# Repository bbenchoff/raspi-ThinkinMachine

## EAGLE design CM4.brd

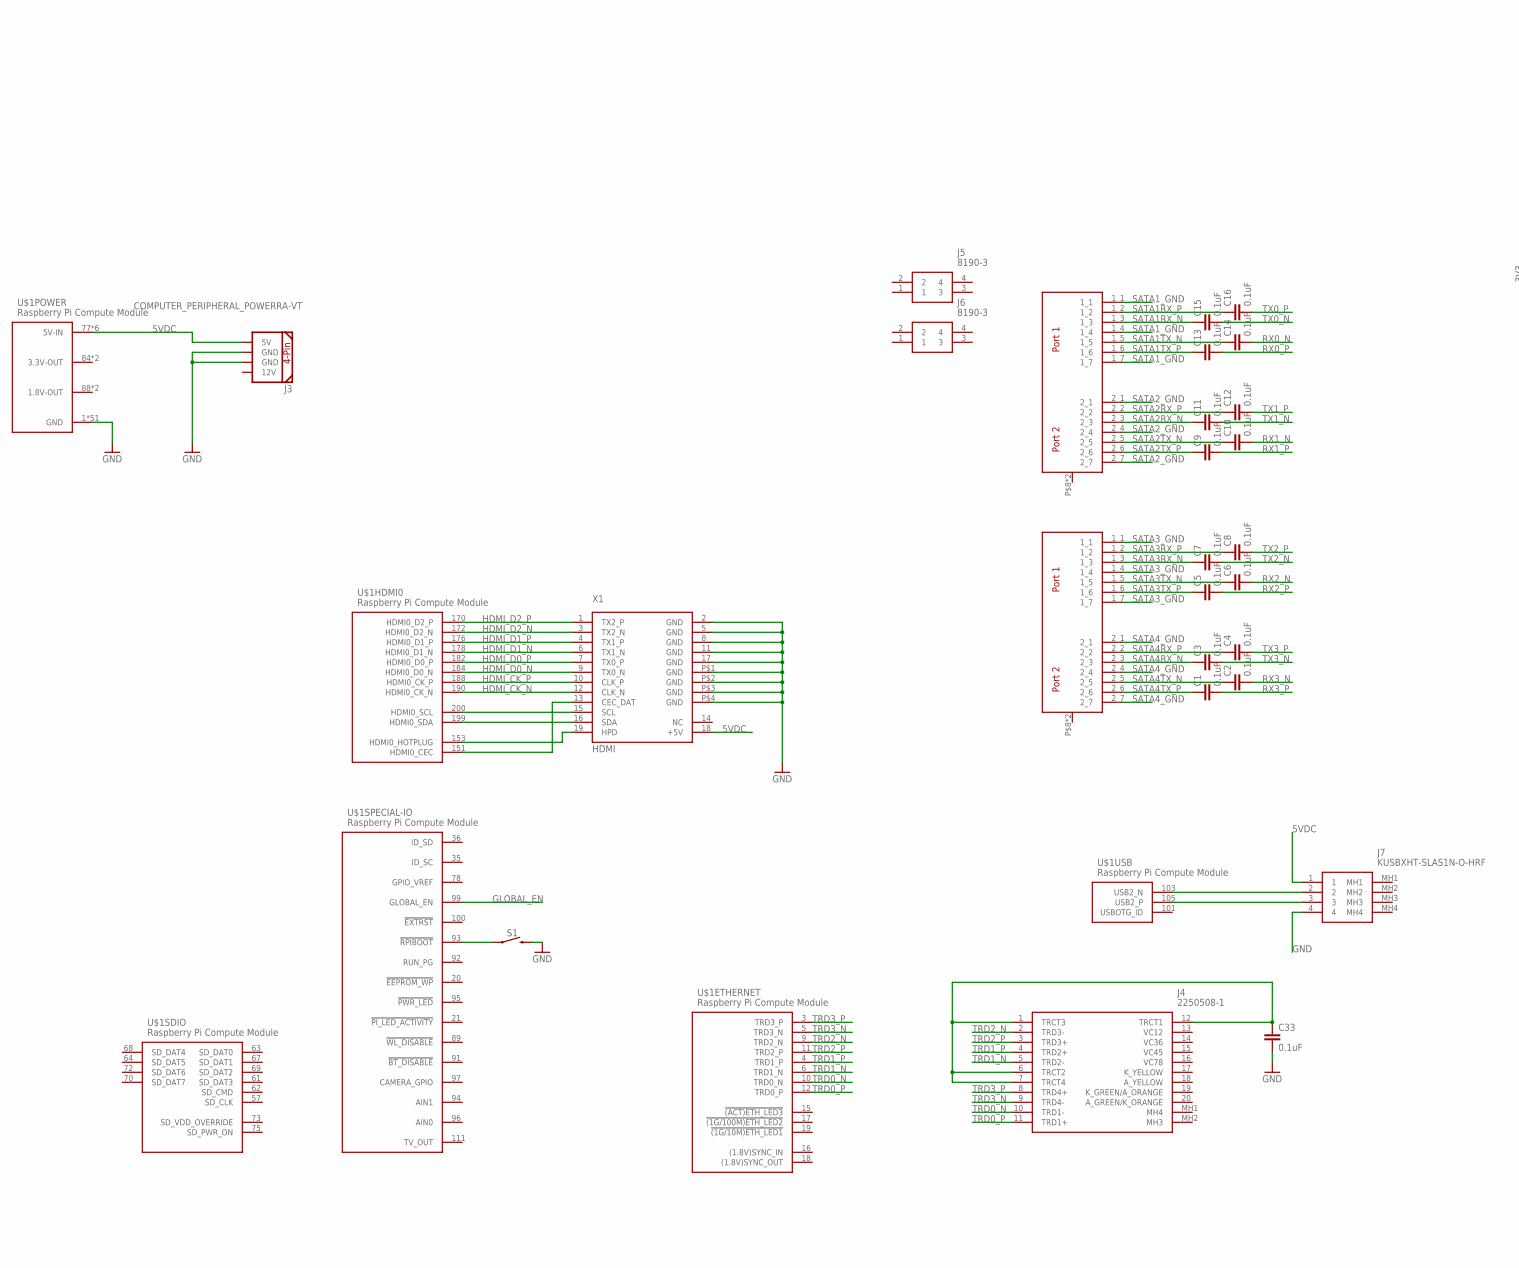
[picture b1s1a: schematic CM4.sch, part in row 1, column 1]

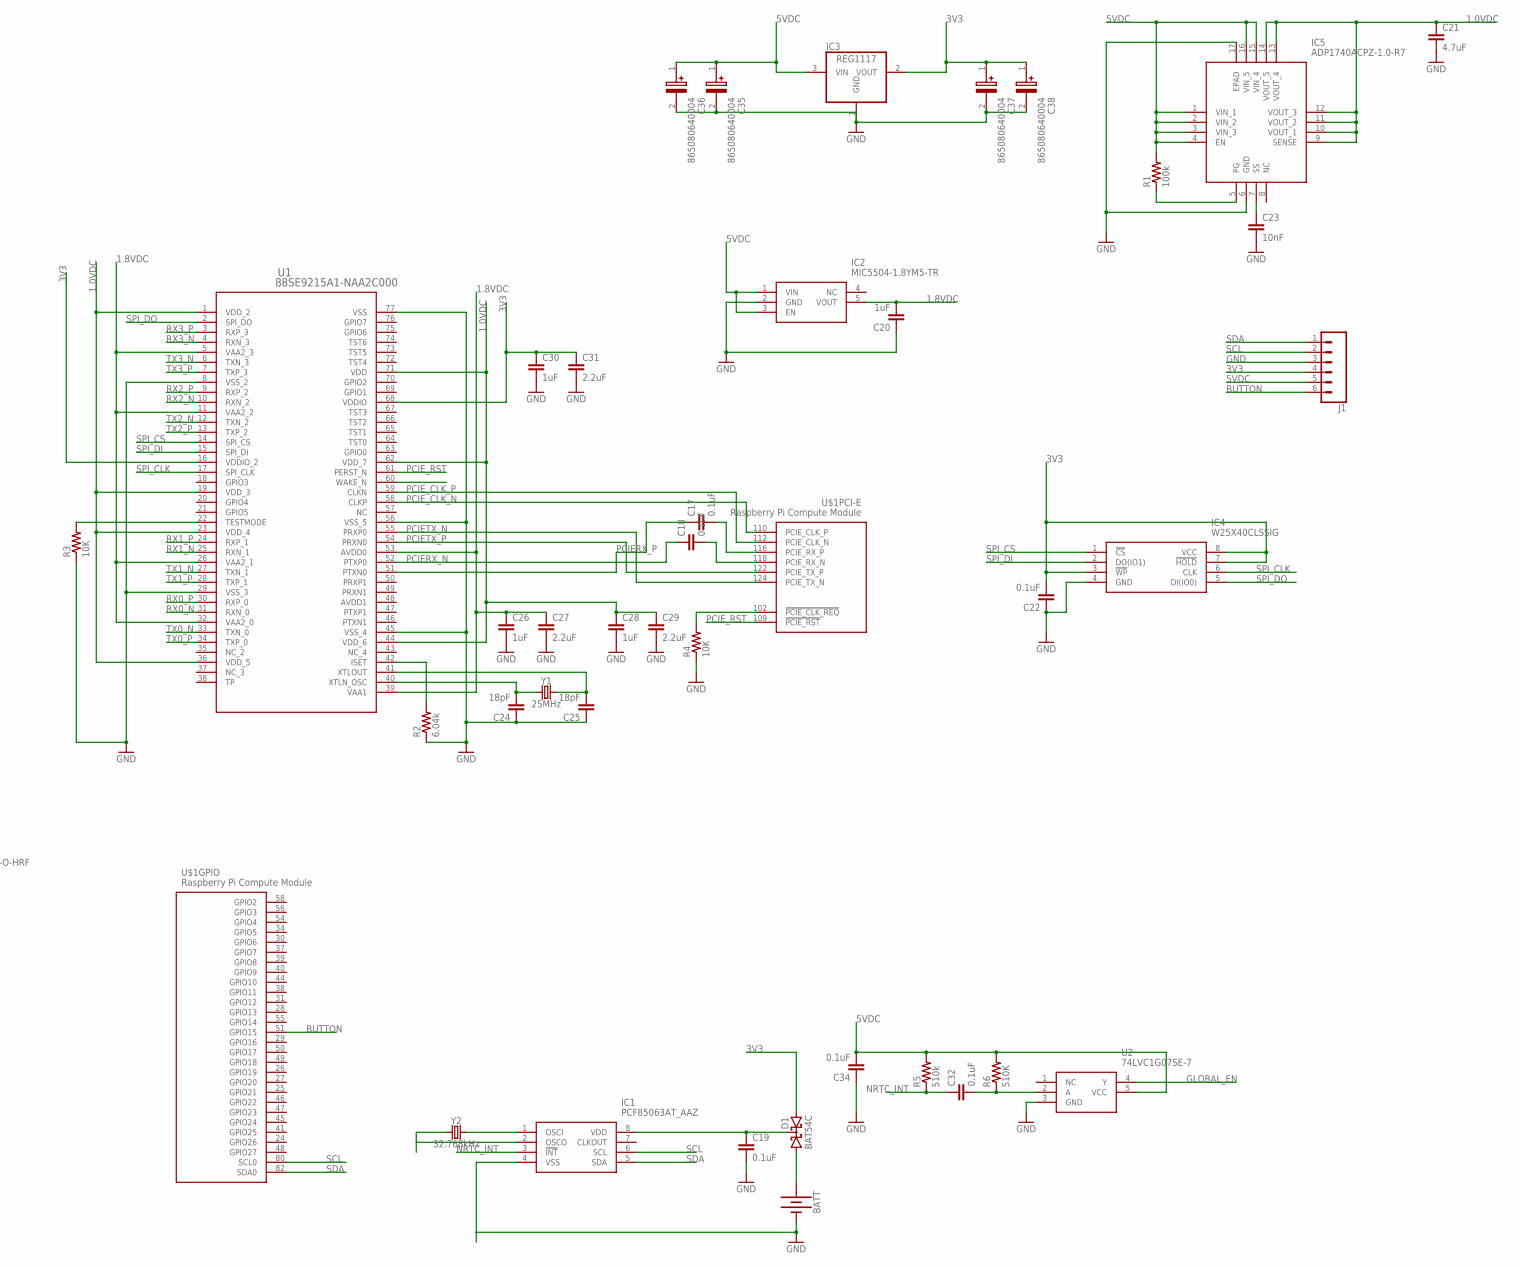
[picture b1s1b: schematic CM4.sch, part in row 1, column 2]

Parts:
BATT: BATTERY-12MM_SMD; BATTCON_12MM
C1, C2, C3, C4, C5, C6, C7, C8, C9, C10, C11, C12, C13, C14, C15, C16, C17, C18, C19, C22, C32, C33, C34: 0.1uF; 0603
C20, C26, C28, C30: 1uF; 0603
C21: 4.7uF; 0603
C23: 10nF; 0603
C24, C25: 18pF; 0603
C27, C29, C31: 2.2uF; 0603
C35, C36, C37, C38: 865080640004
D1: BAT54C; SOT23
IC1: PCF85063AT_AAZ; SOIC127P600X175-8N
IC2: MIC5504-1.8YM5-TR; SOT95P280X145-5N
IC3: REG1117; SOT223
IC4: W25X40CLSSIG; SOIC127P790X216-8N
IC5: ADP1740ACPZ-1.0-R7; QFN65P400X400X80-17N
J1: CONN_06LOCK; 1X06_LOCK
J3: COMPUTER_PERIPHERAL_POWERRA-VT; COMPUTER-PERIPHERAL-POWER-RA-VT
J4: 2250508-1; 22505081
J5, J6: 8190-3; 81903
J7: KUSBXHT-SLAS1N-O-HRF; KUSBXHTSLAS1NOHRF
R1: 100k; R0603
R2: 6.04k; R0603
R3, R4: 10K; R0603
R5: 510k; R0603
R6: 510K; R0603
S1: MOMENTARY-SWITCH-SPST-SMD-5.2-REDUNDANT; TACTILE_SWITCH_SMD_5.2MM
U1: 88SE9215A1-NAA2C000; QFN76_9X9_MTG
U2: 74LVC1G07SE-7; SOT65P210X110-5N
U$1: Raspberry Pi Compute Module; RASPBERRYPI-CM4
U$2, U$3: SATA-D-PL-RT; RIGHTANGLE2PORTSATA
X1: HDMI
Y1: 25MHz; CRYSTAL-SMD-2.0X1.6MM
Y2: 32.768kHz; CRYSTAL-SMD-3.2X1.5MM

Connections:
1.0VDC: C21.1, C28.1, C29.1, IC5.9 (SENSE), IC5.10 (VOUT_1), IC5.11 (VOUT_2), IC5.12 (VOUT_3), IC5.13 (VOUT_4), IC5.14 (VOUT_5), U1.1 (VDD_2), U1.19 (VDD_3), U1.23 (VDD_4), U1.36 (VDD_5), U1.44 (VDD_6), U1.62 (VDD_7), U1.71 (VDD)
1.8V-OUT: U$1.88 (1.8V-OUT), U$1.90 (1.8V-OUT)
1.8VDC: C20.2, C26.1, C27.1, IC2.5 (VOUT), U1.5 (VAA2_3), U1.11 (VAA2_2), U1.26 (VAA2_1), U1.32 (VAA2_0), U1.39 (VAA1), U1.53 (AVDD0)
3.3V-OUT: U$1.84 (3.3V-OUT), U$1.86 (3.3V-OUT)
3V3: C22.2, C30.1, C31.1, C37.1 (+), C38.1 (+), D1.2 (A2), IC3.2 (VOUT), IC4.3 (!WP), IC4.7 (!HOLD), IC4.8 (VCC), J1.4, U1.16 (VDDIO_2), U1.68 (VDDIO)
5VDC: C34.2, C35.1 (+), C36.1 (+), IC2.1 (VIN), IC2.3 (EN), IC3.3 (VIN), IC5.1 (VIN_1), IC5.2 (VIN_2), IC5.3 (VIN_3), IC5.4 (EN), IC5.15 (VIN_4), IC5.16 (VIN_5), J1.5, J3.5V, J7.1, R1.2, R5.2, R6.2, U2.5 (VCC), U$1.77 (5V-IN), U$1.79 (5V-IN), U$1.81 (5V-IN), U$1.83 (5V-IN), U$1.85 (5V-IN), U$1.87 (5V-IN), X1.18 (+5V)
AVDD1: U1.48 (AVDD1)
BUTTON: J1.6, U$1.51 (GPIO15)
GLOBAL_EN: U2.4 (Y), U$1.99 (GLOBAL_EN)
GND: BATT.GND (-), C19.2, C20.1, C21.2, C22.1, C23.2, C24.1, C25.1, C26.2, C27.2, C28.2, C29.2, C30.2, C31.2, C33.2, C34.1, C35.2 (-), C36.2 (-), C37.2 (-), C38.2 (-), IC1.4 (VSS), IC2.2 (GND), IC3.1 (GND), IC4.4 (GND), IC5.6 (GND), IC5.17 (EPAD), J1.3, J3.GND@1 (GND), J3.GND@2 (GND), J7.4, R2.1, R3.1, R4.1, S1.3 (2), S1.4 (2), U1.8 (VSS_2), U1.29 (VSS_3), U1.45 (VSS_4), U1.56 (VSS_5), U1.77 (VSS), U2.3 (GND), U$1.1 (GND), U$1.2 (GND), U$1.7 (GND), U$1.8 (GND), U$1.13 (GND), U$1.14 (GND), U$1.22 (GND), U$1.23 (GND), U$1.32 (GND), U$1.33 (GND), U$1.42 (GND), U$1.43 (GND), U$1.52 (GND), U$1.53 (GND), U$1.59 (GND), U$1.60 (GND), U$1.65 (GND), U$1.66 (GND), U$1.71 (GND), U$1.74 (GND), U$1.98 (GND), U$1.107 (GND), U$1.108 (GND), U$1.113 (GND), U$1.114 (GND), U$1.119 (GND), U$1.120 (GND), U$1.125 (GND), U$1.126 (GND), U$1.131 (GND), U$1.132 (GND), U$1.137 (GND), U$1.138 (GND), U$1.144 (GND), U$1.150 (GND), U$1.155 (GND), U$1.156 (GND), U$1.161 (GND), U$1.162 (GND), U$1.167 (GND), U$1.168 (GND), U$1.173 (GND), U$1.174 (GND), U$1.179 (GND), U$1.180 (GND), U$1.185 (GND), U$1.186 (GND), U$1.191 (GND), U$1.192 (GND), U$1.197 (GND), U$1.198 (GND), X1.2 (GND), X1.5 (GND), X1.8 (GND), X1.11 (GND), X1.17 (GND), X1.P$1 (GND), X1.P$2 (GND), X1.P$3 (GND), X1.P$4 (GND)
HDMI_CK_N: U$1.190 (HDMI0_CK_N), X1.12 (CLK_N)
HDMI_CK_P: U$1.188 (HDMI0_CK_P), X1.10 (CLK_P)
HDMI_D0_N: U$1.184 (HDMI0_D0_N), X1.9 (TX0_N)
HDMI_D0_P: U$1.182 (HDMI0_D0_P), X1.7 (TX0_P)
HDMI_D1_N: U$1.178 (HDMI0_D1_N), X1.6 (TX1_N)
HDMI_D1_P: U$1.176 (HDMI0_D1_P), X1.4 (TX1_P)
HDMI_D2_N: U$1.172 (HDMI0_D2_N), X1.3 (TX2_N)
HDMI_D2_P: U$1.170 (HDMI0_D2_P), X1.1 (TX2_P)
unnamed: C23.1, IC5.7 (SS)
unnamed: IC5.5 (PG), R1.1
unnamed: C24.2, U1.40 (XTLN_OSC), Y1.1
unnamed: C25.2, U1.41 (XTLOUT), Y1.3 (2)
unnamed: C33.1, J4.1 (TRCT3), J4.6 (TRCT2), J4.7 (TRCT4), J4.12 (TRCT1)
unnamed: S1.1, S1.2 (1), U$1.93 (!RPIBOOT)
unnamed: R2.2, U1.42 (ISET)
unnamed: U$1.200 (HDMI0_SCL), X1.15 (SCL)
unnamed: U$1.199 (HDMI0_SDA), X1.16 (SDA)
unnamed: U$1.153 (HDMI0_HOTPLUG), X1.19 (HPD)
unnamed: U$1.151 (HDMI0_CEC), X1.13 (CEC_DAT)
unnamed: IC1.1 (OSCI), Y2.P$2 (2)
unnamed: IC1.2 (OSCO), Y2.P$1 (1)
unnamed: C32.2, R6.1, U2.2 (A)
unnamed: J7.2, U$1.103 (USB2_N)
unnamed: J7.3, U$1.105 (USB2_P)
unnamed: BATT.PWR@1 (+), D1.1 (A1)
unnamed: C19.1, D1.3 (CC), IC1.8 (VDD)
unnamed: R3.2, U1.22 (TESTMODE)
unnamed: R4.2, U$1.102 (!PCIE_CLK_REQ)
NRTC_INT: C32.1, IC1.3 (!INT), R5.1
PCIERXCAP_N: C18.2, U$1.118 (PCIE_RX_N)
PCIERXCAP_P: C17.2, U$1.116 (PCIE_RX_P)
PCIERX_N: C18.1, U1.52 (PTXP0)
PCIERX_P: C17.1, U1.51 (PTXN0)
PCIETX_N: U1.55 (PRXP0), U$1.124 (PCIE_TX_N)
PCIETX_P: U1.54 (PRXN0), U$1.122 (PCIE_TX_P)
PCIE_CLK_N: U1.58 (CLKP), U$1.110 (PCIE_CLK_P)
PCIE_CLK_P: U1.59 (CLKN), U$1.112 (PCIE_CLK_N)
PCIE_RST: U1.61 (PERST_N), U$1.109 (!PCIE_RST)
RX0_N: C14.2, U1.31 (RXN_0)
RX0_P: C13.2, U1.30 (RXP_0)
RX1_N: C10.2, U1.25 (RXN_1)
RX1_P: C9.2, U1.24 (RXP_1)
RX2_N: C6.2, U1.10 (RXN_2)
RX2_P: C5.2, U1.9 (RXP_2)
RX3_N: C2.2, U1.4 (RXN_3)
RX3_P: C1.2, U1.3 (RXP_3)
SATA1RX_N: C15.1, U$2.1_3
SATA1RX_P: C16.1, U$2.1_2
SATA1TX_N: C14.1, U$2.1_5
SATA1TX_P: C13.1, U$2.1_6
SATA1_GND: U$2.1_1, U$2.1_4, U$2.1_7
SATA2RX_N: C11.1, U$2.2_3
SATA2RX_P: C12.1, U$2.2_2
SATA2TX_N: C10.1, U$2.2_5
SATA2TX_P: C9.1, U$2.2_6
SATA2_GND: U$2.2_1, U$2.2_4, U$2.2_7
SATA3RX_N: C7.1, U$3.1_3
SATA3RX_P: C8.1, U$3.1_2
SATA3TX_N: C6.1, U$3.1_5
SATA3TX_P: C5.1, U$3.1_6
SATA3_GND: U$3.1_1, U$3.1_4, U$3.1_7
SATA4RX_N: C3.1, U$3.2_3
SATA4RX_P: C4.1, U$3.2_2
SATA4TX_N: C2.1, U$3.2_5
SATA4TX_P: C1.1, U$3.2_6
SATA4_GND: U$3.2_1, U$3.2_4, U$3.2_7
SCL: IC1.6 (SCL), J1.2, U$1.80 (SCL0)
SDA: IC1.5 (SDA), J1.1, U$1.82 (SDA0)
SPI_CLK: IC4.6 (CLK), U1.17 (SPI_CLK)
SPI_CS: IC4.1 (!CS), U1.14 (SPI_CS)
SPI_DI: IC4.2 (DO(IO1)), U1.15 (SPI_DI)
SPI_DO: IC4.5 (DI(IO0)), U1.2 (SPI_DO)
TRD0_N: J4.10 (TRD1-), U$1.10 (TRD0_N)
TRD0_P: J4.11 (TRD1+), U$1.12 (TRD0_P)
TRD1_N: J4.5 (TRD2-), U$1.6 (TRD1_N)
TRD1_P: J4.4 (TRD2+), U$1.4 (TRD1_P)
TRD2_N: J4.2 (TRD3-), U$1.9 (TRD2_N)
TRD2_P: J4.3 (TRD3+), U$1.11 (TRD2_P)
TRD3_N: J4.9 (TRD4-), U$1.5 (TRD3_N)
TRD3_P: J4.8 (TRD4+), U$1.3 (TRD3_P)
TX0_N: C15.2, U1.33 (TXN_0)
TX0_P: C16.2, U1.34 (TXP_0)
TX1_N: C11.2, U1.27 (TXN_1)
TX1_P: C12.2, U1.28 (TXP_1)
TX2_N: C7.2, U1.12 (TXN_2)
TX2_P: C8.2, U1.13 (TXP_2)
TX3_N: C3.2, U1.6 (TXN_3)
TX3_P: C4.2, U1.7 (TXP_3)

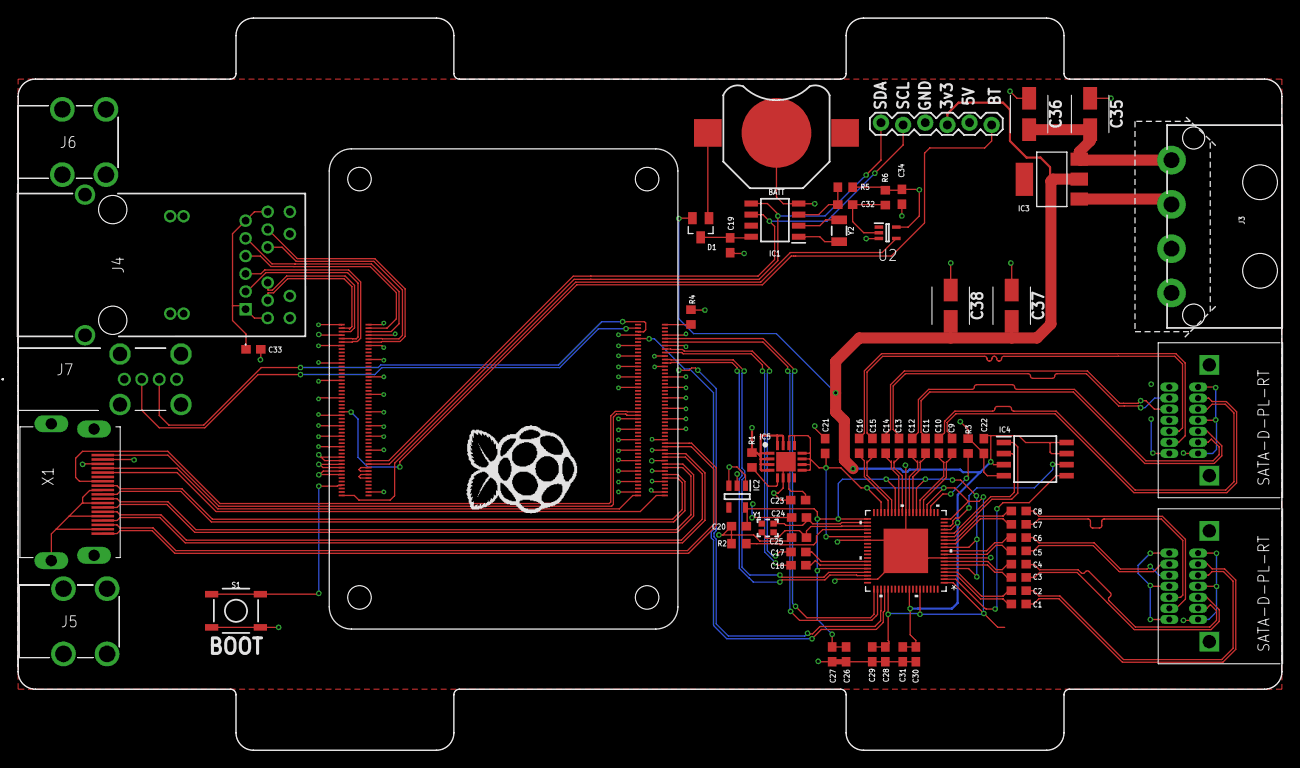
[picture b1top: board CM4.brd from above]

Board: 4 copper layers, 145.0 x 84.0 mm, 66 parts (0 on the bottom side), 97 nets.

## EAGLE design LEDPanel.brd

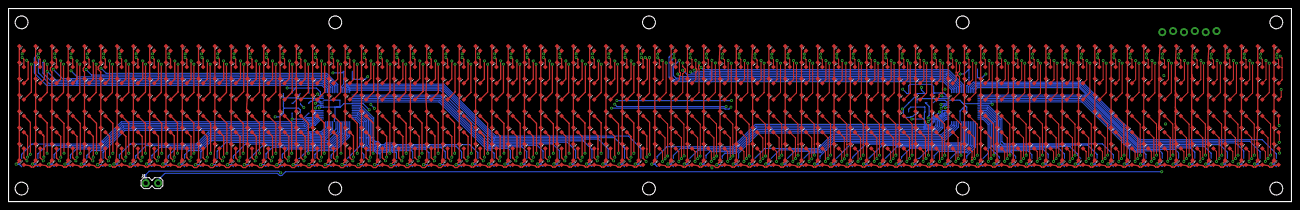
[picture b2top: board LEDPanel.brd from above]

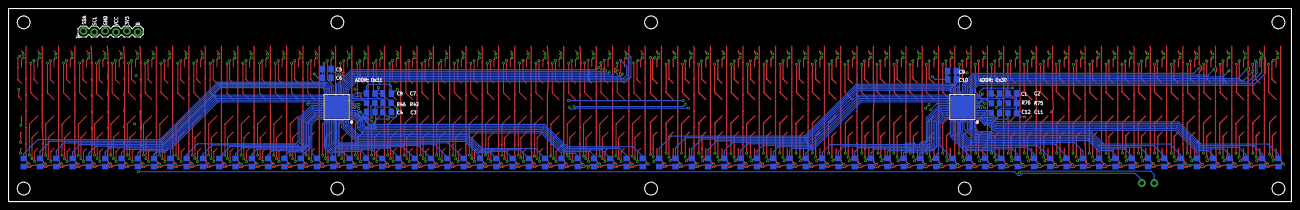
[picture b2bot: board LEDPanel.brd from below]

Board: 4 copper layers, 300.0 x 45.1 mm, 722 parts (97 on the bottom side), 182 nets.

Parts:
C1, C3, C5, C7, C9, C11: 0.1uF; C0805K
C2, C4, C6, C8, C10, C12: 1uF; C0805K
J1: 1X02_LOCK
J4: 1X06_LOCK
LED1, LED2, LED3, LED4, LED5, LED6, LED7, LED8, LED9, LED10, LED11, LED12, LED13, LED14, LED15, LED16, LED17, LED18, LED19, LED20, LED21, LED22, LED23, LED24, LED25, LED26, LED27, LED28, LED29, LED30, LED31, LED32, LED33, LED34, LED35, LED36, LED37, LED38, LED39, LED40, LED41, LED42, LED43, LED44, LED45, LED46, LED47, LED48, LED49, LED50, LED51, LED52, LED53, LED54, LED55, LED56, LED57, LED58, LED59, LED60, LED61, LED62, LED63, LED64, LED65, LED66, LED67, LED68, LED69, LED70, LED71, LED72, LED73, LED74, LED75, LED76, LED77, LED78, LED79, LED80, LED81, LED82, LED83, LED84, LED85, LED86, LED87, LED88, LED89, LED90, LED91, LED92, LED93, LED94, LED95, LED96, LED97, LED98, LED99, LED100, LED101, LED102, LED103, LED104, LED105, LED106, LED107, LED108, LED109, LED110, LED111, LED112, LED113, LED114, LED115, LED116, LED117, LED118, LED119, LED120, LED121, LED122, LED123, LED124, LED125, LED126, LED127, LED128, LED129, LED130, LED131, LED132, LED133, LED134, LED135, LED136, LED137, LED138, LED139, LED140, LED141, LED142, LED143, LED144, LED145, LED146, LED147, LED148, LED149, LED150, LED151, LED152, LED153, LED154, LED155, LED156, LED157, LED158, LED159, LED160, LED161, LED162, LED163, LED164, LED165, LED166, LED167, LED168, LED169, LED170, LED171, LED172, LED173, LED174, LED175, LED176, LED177, LED178, LED179, LED180, LED181, LED182, LED183, LED184, LED185, LED186, LED187, LED188, LED189, LED190, LED191, LED192, LED193, LED194, LED195, LED196, LED197, LED198, LED199, LED200, LED201, LED202, LED203, LED204, LED205, LED206, LED207, LED208, LED209, LED210, LED211, LED212, LED213, LED214, LED215, LED216, LED217, LED218, LED219, LED220, LED221, LED222, LED223, LED224, LED225, LED226, LED227, LED228, LED229, LED230, LED231, LED232, LED233, LED234, LED235, LED236, LED237, LED238, LED239, LED240, LED241, LED242, LED243, LED244, LED245, LED246, LED247, LED248, LED249, LED250, LED251, LED252, LED253, LED254, LED255, LED256, LED257, LED258, LED259, LED260, LED261, LED262, LED263, LED264, LED265, LED266, LED267, LED268, LED269, LED270, LED271, LED272, LED273, LED274, LED275, LED276, LED277, LED278, LED279, LED280, LED281, LED282, LED283, LED284, LED285, LED286, LED287, LED288, LED289, LED290, LED291, LED292, LED293, LED294, LED295, LED296, LED297, LED298, LED299, LED300, LED301, LED302, LED303, LED304, LED305, LED306, LED307, LED308, LED309, LED310, LED311, LED312, LED313, LED314, LED315, LED316, LED317, LED318, LED319, LED320, LED321, LED322, LED323, LED324, LED325, LED326, LED327, LED328, LED329, LED330, LED331, LED332, LED333, LED334, LED335, LED336, LED337, LED338, LED339, LED340, LED341, LED342, LED343, LED344, LED345, LED346, LED347, LED348, LED349, LED350, LED351, LED352, LED353, LED354, LED355, LED356, LED357, LED358, LED359, LED360, LED361, LED362, LED363, LED364, LED365, LED366, LED367, LED368, LED369, LED370, LED371, LED372, LED373, LED374, LED375, LED376, LED377, LED378, LED379, LED380, LED381, LED382, LED383, LED384, LED385, LED386, LED387, LED388, LED389, LED390, LED391, LED392, LED393, LED394, LED395, LED396, LED397, LED398, LED399, LED400, LED401, LED402, LED403, LED404, LED405, LED406, LED407, LED408, LED409, LED410, LED411, LED412, LED413, LED414, LED415, LED416, LED417, LED418, LED419, LED420, LED421, LED422, LED423, LED424, LED425, LED426, LED427, LED428, LED429, LED430, LED431, LED432, LED433, LED434, LED435, LED436, LED437, LED438, LED439, LED440, LED441, LED442, LED443, LED444, LED445, LED446, LED447, LED448, LED449, LED450, LED451, LED452, LED453, LED454, LED455, LED456, LED457, LED458, LED459, LED460, LED461, LED462, LED463, LED464, LED465, LED466, LED467, LED468, LED469, LED470, LED471, LED472, LED473, LED474, LED475, LED476, LED477, LED478, LED479, LED480, LED481, LED482, LED483, LED484, LED485, LED486, LED487, LED488, LED489, LED490, LED491, LED492, LED493, LED494, LED495, LED496, LED497, LED498, LED499, LED500, LED501, LED502, LED503, LED504, LED505, LED506, LED507, LED508, LED509, LED510, LED511, LED512, LED513, LED514, LED515, LED516, LED517, LED518, LED519, LED520, LED521, LED522, LED523, LED524, LED525, LED526, LED527, LED528, LED529, LED530, LED531, LED532, LED533, LED534, LED535, LED536, LED537, LED538, LED539, LED540, LED541, LED542, LED543, LED544, LED545, LED546, LED547, LED548, LED549, LED550, LED551, LED552, LED553, LED554, LED555, LED556, LED557, LED558, LED559, LED560, LED561, LED562, LED563, LED564, LED565, LED566, LED567, LED568, LED569, LED570, LED571, LED572, LED573, LED574, LED575, LED576, LED577, LED578, LED579, LED580, LED581, LED582, LED583, LED584, LED585, LED586, LED587, LED588, LED589, LED590, LED591, LED592, LED593, LED594, LED595, LED596, LED597, LED598, LED599, LED600, LED601, LED602, LED603, LED604, LED605, LED606, LED607, LED608, LED609, LED610, LED611, LED612, LED613, LED614, LED615, LED616, LED617, LED618, LED619, LED620, LED621, LED622, LED623, LED624: CHIP-LED0603
R1, R2, R3, R4, R5, R6, R7, R8, R9, R10, R11, R12, R13, R14, R15, R16, R17, R18, R19, R20, R21, R22, R23, R24, R25, R26, R27, R28, R29, R30, R31, R32, R33, R34, R35, R36, R37, R38, R39, R40, R41, R43, R44, R45, R47, R48, R49, R50, R51, R52, R53, R54, R55, R56, R57, R58, R59, R60, R61, R62, R63, R64, R65, R66, R67, R68, R69, R70, R71, R72, R73, R74, R77, R78, R79, R80, R81, R82: 68; R0805
R42, R46, R75, R76: 10k; R0805
U1, U2: IS31FL3741_QFN60; QFN60

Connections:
3V3: J1.1, J4.5, R46.2, R76.2, U1.8
BUTTON: J1.2, J4.6
GND: C1.2, C2.2, C3.2, C4.2, C5.2, C6.2, C7.2, C8.2, C9.2, C10.2, C11.2, C12.2, J4.3, R42.1, R75.1, U1.12, U1.36, U1.55, U1.PAD, U2.8, U2.12, U2.36, U2.55, U2.PAD
unnamed: R57.1, U2.26
unnamed: R58.1, U2.27
unnamed: R59.1, U2.28
unnamed: R60.1, U2.29
unnamed: R61.1, U2.30
unnamed: R62.1, U2.31
unnamed: R63.1, U2.32
unnamed: R64.1, U2.33
unnamed: R65.1, U2.34
unnamed: R66.1, U2.35
unnamed: R67.1, U2.37
unnamed: R68.1, U2.38
unnamed: R69.1, U2.39
unnamed: R70.1, U2.40
unnamed: R71.1, U2.41
unnamed: R72.1, U2.42
unnamed: R73.1, U2.43
unnamed: R74.1, U2.44
unnamed: R56.1, U2.45
unnamed: R55.1, U2.46
unnamed: R54.1, U2.47
unnamed: R53.1, U2.48
unnamed: R52.1, U2.49
unnamed: R51.1, U2.50
unnamed: R50.1, U2.51
unnamed: R49.1, U2.52
unnamed: R48.1, U2.53
unnamed: R47.1, U2.54
unnamed: R45.1, U2.56
unnamed: R44.1, U2.57
unnamed: R43.1, U2.58
unnamed: R41.1, U2.59
unnamed: R40.1, U2.60
unnamed: R39.1, U2.1
unnamed: R38.1, U2.2
unnamed: R37.1, U2.3
unnamed: R75.2, U2.13
unnamed: R76.1, U2.11
unnamed: R82.1, U2.4
unnamed: R81.1, U2.5
unnamed: R80.1, U2.6
unnamed: R22.1, U1.26
unnamed: R46.1, U1.11
unnamed: R42.2, U1.13
unnamed: R1.1, U1.27
unnamed: R2.1, U1.28
unnamed: R3.1, U1.29
unnamed: R23.1, U1.30
unnamed: R24.1, U1.31
unnamed: R25.1, U1.32
unnamed: R26.1, U1.33
unnamed: R27.1, U1.34
unnamed: R28.1, U1.35
unnamed: R29.1, U1.37
unnamed: R30.1, U1.38
unnamed: R31.1, U1.39
unnamed: R32.1, U1.40
unnamed: R33.1, U1.41
unnamed: R34.1, U1.42
unnamed: R35.1, U1.43
unnamed: R36.1, U1.44
unnamed: R21.1, U1.45
unnamed: R20.1, U1.46
unnamed: R19.1, U1.47
unnamed: R18.1, U1.48
unnamed: R17.1, U1.49
unnamed: R16.1, U1.50
unnamed: R15.1, U1.51
unnamed: R14.1, U1.52
unnamed: R13.1, U1.53
unnamed: R12.1, U1.54
unnamed: R11.1, U1.56
unnamed: R10.1, U1.57
unnamed: R9.1, U1.58
unnamed: R8.1, U1.59
unnamed: R7.1, U1.60
unnamed: R6.1, U1.1
unnamed: R5.1, U1.2
unnamed: R4.1, U1.3
unnamed: R79.1, U1.4
unnamed: R78.1, U1.5
unnamed: R77.1, U1.6
unnamed: LED617.C, LED618.C, LED619.C, LED620.C, LED621.C, LED622.C, LED623.C, LED624.C, R22.2
unnamed: LED609.C, LED610.C, LED611.C, LED612.C, LED613.C, LED614.C, LED615.C, LED616.C, R1.2
unnamed: LED601.C, LED602.C, LED603.C, LED604.C, LED605.C, LED606.C, LED607.C, LED608.C, R2.2
unnamed: LED593.C, LED594.C, LED595.C, LED596.C, LED597.C, LED598.C, LED599.C, LED600.C, R3.2
unnamed: LED585.C, LED586.C, LED587.C, LED588.C, LED589.C, LED590.C, LED591.C, LED592.C, R23.2
unnamed: LED577.C, LED578.C, LED579.C, LED580.C, LED581.C, LED582.C, LED583.C, LED584.C, R24.2
unnamed: LED569.C, LED570.C, LED571.C, LED572.C, LED573.C, LED574.C, LED575.C, LED576.C, R25.2
unnamed: LED561.C, LED562.C, LED563.C, LED564.C, LED565.C, LED566.C, LED567.C, LED568.C, R26.2
unnamed: LED553.C, LED554.C, LED555.C, LED556.C, LED557.C, LED558.C, LED559.C, LED560.C, R27.2
unnamed: LED545.C, LED546.C, LED547.C, LED548.C, LED549.C, LED550.C, LED551.C, LED552.C, R28.2
unnamed: LED537.C, LED538.C, LED539.C, LED540.C, LED541.C, LED542.C, LED543.C, LED544.C, R29.2
unnamed: LED529.C, LED530.C, LED531.C, LED532.C, LED533.C, LED534.C, LED535.C, LED536.C, R30.2
unnamed: LED521.C, LED522.C, LED523.C, LED524.C, LED525.C, LED526.C, LED527.C, LED528.C, R31.2
unnamed: LED513.C, LED514.C, LED515.C, LED516.C, LED517.C, LED518.C, LED519.C, LED520.C, R32.2
unnamed: LED505.C, LED506.C, LED507.C, LED508.C, LED509.C, LED510.C, LED511.C, LED512.C, R33.2
unnamed: LED497.C, LED498.C, LED499.C, LED500.C, LED501.C, LED502.C, LED503.C, LED504.C, R34.2
unnamed: LED489.C, LED490.C, LED491.C, LED492.C, LED493.C, LED494.C, LED495.C, LED496.C, R35.2
unnamed: LED481.C, LED482.C, LED483.C, LED484.C, LED485.C, LED486.C, LED487.C, LED488.C, R36.2
unnamed: LED473.C, LED474.C, LED475.C, LED476.C, LED477.C, LED478.C, LED479.C, LED480.C, R21.2
unnamed: LED465.C, LED466.C, LED467.C, LED468.C, LED469.C, LED470.C, LED471.C, LED472.C, R20.2
unnamed: LED457.C, LED458.C, LED459.C, LED460.C, LED461.C, LED462.C, LED463.C, LED464.C, R19.2
unnamed: LED449.C, LED450.C, LED451.C, LED452.C, LED453.C, LED454.C, LED455.C, LED456.C, R18.2
unnamed: LED441.C, LED442.C, LED443.C, LED444.C, LED445.C, LED446.C, LED447.C, LED448.C, R17.2
unnamed: LED433.C, LED434.C, LED435.C, LED436.C, LED437.C, LED438.C, LED439.C, LED440.C, R16.2
unnamed: LED425.C, LED426.C, LED427.C, LED428.C, LED429.C, LED430.C, LED431.C, LED432.C, R15.2
unnamed: LED417.C, LED418.C, LED419.C, LED420.C, LED421.C, LED422.C, LED423.C, LED424.C, R14.2
unnamed: LED409.C, LED410.C, LED411.C, LED412.C, LED413.C, LED414.C, LED415.C, LED416.C, R13.2
unnamed: LED401.C, LED402.C, LED403.C, LED404.C, LED405.C, LED406.C, LED407.C, LED408.C, R12.2
unnamed: LED393.C, LED394.C, LED395.C, LED396.C, LED397.C, LED398.C, LED399.C, LED400.C, R11.2
unnamed: LED385.C, LED386.C, LED387.C, LED388.C, LED389.C, LED390.C, LED391.C, LED392.C, R10.2
unnamed: LED377.C, LED378.C, LED379.C, LED380.C, LED381.C, LED382.C, LED383.C, LED384.C, R9.2
unnamed: LED369.C, LED370.C, LED371.C, LED372.C, LED373.C, LED374.C, LED375.C, LED376.C, R8.2
unnamed: LED361.C, LED362.C, LED363.C, LED364.C, LED365.C, LED366.C, LED367.C, LED368.C, R7.2
unnamed: LED353.C, LED354.C, LED355.C, LED356.C, LED357.C, LED358.C, LED359.C, LED360.C, R6.2
unnamed: LED345.C, LED346.C, LED347.C, LED348.C, LED349.C, LED350.C, LED351.C, LED352.C, R5.2
unnamed: LED337.C, LED338.C, LED339.C, LED340.C, LED341.C, LED342.C, LED343.C, LED344.C, R4.2
unnamed: LED329.C, LED330.C, LED331.C, LED332.C, LED333.C, LED334.C, LED335.C, LED336.C, R79.2
unnamed: LED321.C, LED322.C, LED323.C, LED324.C, LED325.C, LED326.C, LED327.C, LED328.C, R78.2
unnamed: LED313.C, LED314.C, LED315.C, LED316.C, LED317.C, LED318.C, LED319.C, LED320.C, R77.2
unnamed: LED305.C, LED306.C, LED307.C, LED308.C, LED309.C, LED310.C, LED311.C, LED312.C, R57.2
unnamed: LED297.C, LED298.C, LED299.C, LED300.C, LED301.C, LED302.C, LED303.C, LED304.C, R58.2
unnamed: LED289.C, LED290.C, LED291.C, LED292.C, LED293.C, LED294.C, LED295.C, LED296.C, R59.2
unnamed: LED281.C, LED282.C, LED283.C, LED284.C, LED285.C, LED286.C, LED287.C, LED288.C, R60.2
unnamed: LED273.C, LED274.C, LED275.C, LED276.C, LED277.C, LED278.C, LED279.C, LED280.C, R61.2
unnamed: LED265.C, LED266.C, LED267.C, LED268.C, LED269.C, LED270.C, LED271.C, LED272.C, R62.2
unnamed: LED257.C, LED258.C, LED259.C, LED260.C, LED261.C, LED262.C, LED263.C, LED264.C, R63.2
unnamed: LED249.C, LED250.C, LED251.C, LED252.C, LED253.C, LED254.C, LED255.C, LED256.C, R64.2
unnamed: LED241.C, LED242.C, LED243.C, LED244.C, LED245.C, LED246.C, LED247.C, LED248.C, R65.2
unnamed: LED233.C, LED234.C, LED235.C, LED236.C, LED237.C, LED238.C, LED239.C, LED240.C, R66.2
unnamed: LED225.C, LED226.C, LED227.C, LED228.C, LED229.C, LED230.C, LED231.C, LED232.C, R67.2
unnamed: LED217.C, LED218.C, LED219.C, LED220.C, LED221.C, LED222.C, LED223.C, LED224.C, R68.2
unnamed: LED209.C, LED210.C, LED211.C, LED212.C, LED213.C, LED214.C, LED215.C, LED216.C, R69.2
unnamed: LED201.C, LED202.C, LED203.C, LED204.C, LED205.C, LED206.C, LED207.C, LED208.C, R70.2
unnamed: LED193.C, LED194.C, LED195.C, LED196.C, LED197.C, LED198.C, LED199.C, LED200.C, R71.2
unnamed: LED185.C, LED186.C, LED187.C, LED188.C, LED189.C, LED190.C, LED191.C, LED192.C, R72.2
unnamed: LED177.C, LED178.C, LED179.C, LED180.C, LED181.C, LED182.C, LED183.C, LED184.C, R73.2
unnamed: LED169.C, LED170.C, LED171.C, LED172.C, LED173.C, LED174.C, LED175.C, LED176.C, R74.2
unnamed: LED161.C, LED162.C, LED163.C, LED164.C, LED165.C, LED166.C, LED167.C, LED168.C, R56.2
unnamed: LED153.C, LED154.C, LED155.C, LED156.C, LED157.C, LED158.C, LED159.C, LED160.C, R55.2
unnamed: LED145.C, LED146.C, LED147.C, LED148.C, LED149.C, LED150.C, LED151.C, LED152.C, R54.2
unnamed: LED137.C, LED138.C, LED139.C, LED140.C, LED141.C, LED142.C, LED143.C, LED144.C, R53.2
unnamed: LED129.C, LED130.C, LED131.C, LED132.C, LED133.C, LED134.C, LED135.C, LED136.C, R52.2
unnamed: LED121.C, LED122.C, LED123.C, LED124.C, LED125.C, LED126.C, LED127.C, LED128.C, R51.2
unnamed: LED113.C, LED114.C, LED115.C, LED116.C, LED117.C, LED118.C, LED119.C, LED120.C, R50.2
unnamed: LED105.C, LED106.C, LED107.C, LED108.C, LED109.C, LED110.C, LED111.C, LED112.C, R49.2
unnamed: LED97.C, LED98.C, LED99.C, LED100.C, LED101.C, LED102.C, LED103.C, LED104.C, R48.2
unnamed: LED89.C, LED90.C, LED91.C, LED92.C, LED93.C, LED94.C, LED95.C, LED96.C, R47.2
unnamed: LED81.C, LED82.C, LED83.C, LED84.C, LED85.C, LED86.C, LED87.C, LED88.C, R45.2
unnamed: LED73.C, LED74.C, LED75.C, LED76.C, LED77.C, LED78.C, LED79.C, LED80.C, R44.2
unnamed: LED65.C, LED66.C, LED67.C, LED68.C, LED69.C, LED70.C, LED71.C, LED72.C, R43.2
unnamed: LED57.C, LED58.C, LED59.C, LED60.C, LED61.C, LED62.C, LED63.C, LED64.C, R41.2
unnamed: LED49.C, LED50.C, LED51.C, LED52.C, LED53.C, LED54.C, LED55.C, LED56.C, R40.2
unnamed: LED41.C, LED42.C, LED43.C, LED44.C, LED45.C, LED46.C, LED47.C, LED48.C, R39.2
unnamed: LED33.C, LED34.C, LED35.C, LED36.C, LED37.C, LED38.C, LED39.C, LED40.C, R38.2
unnamed: LED25.C, LED26.C, LED27.C, LED28.C, LED29.C, LED30.C, LED31.C, LED32.C, R37.2
unnamed: LED17.C, LED18.C, LED19.C, LED20.C, LED21.C, LED22.C, LED23.C, LED24.C, R82.2
unnamed: LED9.C, LED10.C, LED11.C, LED12.C, LED13.C, LED14.C, LED15.C, LED16.C, R81.2
unnamed: LED1.C, LED2.C, LED3.C, LED4.C, LED5.C, LED6.C, LED7.C, LED8.C, R80.2
unnamed: LED316.A, LED324.A, LED332.A, LED340.A, LED348.A, LED356.A, LED364.A, LED372.A, LED380.A, LED388.A, LED396.A, LED404.A, LED412.A, LED420.A, LED428.A, LED436.A, LED444.A, LED452.A, LED460.A, LED468.A, LED476.A, LED484.A, LED492.A, LED500.A, LED508.A, LED516.A, LED524.A, LED532.A, LED540.A, LED548.A, LED556.A, LED564.A, LED572.A, LED580.A, LED588.A, LED596.A, LED604.A, LED612.A, LED620.A, U1.20
unnamed: LED317.A, LED325.A, LED333.A, LED341.A, LED349.A, LED357.A, LED365.A, LED373.A, LED381.A, LED389.A, LED397.A, LED405.A, LED413.A, LED421.A, LED429.A, LED437.A, LED445.A, LED453.A, LED461.A, LED469.A, LED477.A, LED485.A, LED493.A, LED501.A, LED509.A, LED517.A, LED525.A, LED533.A, LED541.A, LED549.A, LED557.A, LED565.A, LED573.A, LED581.A, LED589.A, LED597.A, LED605.A, LED613.A, LED621.A, U1.19
unnamed: LED318.A, LED326.A, LED334.A, LED342.A, LED350.A, LED358.A, LED366.A, LED374.A, LED382.A, LED390.A, LED398.A, LED406.A, LED414.A, LED422.A, LED430.A, LED438.A, LED446.A, LED454.A, LED462.A, LED470.A, LED478.A, LED486.A, LED494.A, LED502.A, LED510.A, LED518.A, LED526.A, LED534.A, LED542.A, LED550.A, LED558.A, LED566.A, LED574.A, LED582.A, LED590.A, LED598.A, LED606.A, LED614.A, LED622.A, U1.18
unnamed: LED319.A, LED327.A, LED335.A, LED343.A, LED351.A, LED359.A, LED367.A, LED375.A, LED383.A, LED391.A, LED399.A, LED407.A, LED415.A, LED423.A, LED431.A, LED439.A, LED447.A, LED455.A, LED463.A, LED471.A, LED479.A, LED487.A, LED495.A, LED503.A, LED511.A, LED519.A, LED527.A, LED535.A, LED543.A, LED551.A, LED559.A, LED567.A, LED575.A, LED583.A, LED591.A, LED599.A, LED607.A, LED615.A, LED623.A, U1.17
unnamed: LED320.A, LED328.A, LED336.A, LED344.A, LED352.A, LED360.A, LED368.A, LED376.A, LED384.A, LED392.A, LED400.A, LED408.A, LED416.A, LED424.A, LED432.A, LED440.A, LED448.A, LED456.A, LED464.A, LED472.A, LED480.A, LED488.A, LED496.A, LED504.A, LED512.A, LED520.A, LED528.A, LED536.A, LED544.A, LED552.A, LED560.A, LED568.A, LED576.A, LED584.A, LED592.A, LED600.A, LED608.A, LED616.A, LED624.A, U1.16
unnamed: LED8.A, LED16.A, LED24.A, LED32.A, LED40.A, LED48.A, LED56.A, LED64.A, LED72.A, LED80.A, LED88.A, LED96.A, LED104.A, LED112.A, LED120.A, LED128.A, LED136.A, LED144.A, LED152.A, LED160.A, LED168.A, LED176.A, LED184.A, LED192.A, LED200.A, LED208.A, LED216.A, LED224.A, LED232.A, LED240.A, LED248.A, LED256.A, LED264.A, LED272.A, LED280.A, LED288.A, LED296.A, LED304.A, LED312.A, U2.16
unnamed: LED7.A, LED15.A, LED23.A, LED31.A, LED39.A, LED47.A, LED55.A, LED63.A, LED71.A, LED79.A, LED87.A, LED95.A, LED103.A, LED111.A, LED119.A, LED127.A, LED135.A, LED143.A, LED151.A, LED159.A, LED167.A, LED175.A, LED183.A, LED191.A, LED199.A, LED207.A, LED215.A, LED223.A, LED231.A, LED239.A, LED247.A, LED255.A, LED263.A, LED271.A, LED279.A, LED287.A, LED295.A, LED303.A, LED311.A, U2.17
unnamed: LED6.A, LED14.A, LED22.A, LED30.A, LED38.A, LED46.A, LED54.A, LED62.A, LED70.A, LED78.A, LED86.A, LED94.A, LED102.A, LED110.A, LED118.A, LED126.A, LED134.A, LED142.A, LED150.A, LED158.A, LED166.A, LED174.A, LED182.A, LED190.A, LED198.A, LED206.A, LED214.A, LED222.A, LED230.A, LED238.A, LED246.A, LED254.A, LED262.A, LED270.A, LED278.A, LED286.A, LED294.A, LED302.A, LED310.A, U2.18
unnamed: LED5.A, LED13.A, LED21.A, LED29.A, LED37.A, LED45.A, LED53.A, LED61.A, LED69.A, LED77.A, LED85.A, LED93.A, LED101.A, LED109.A, LED117.A, LED125.A, LED133.A, LED141.A, LED149.A, LED157.A, LED165.A, LED173.A, LED181.A, LED189.A, LED197.A, LED205.A, LED213.A, LED221.A, LED229.A, LED237.A, LED245.A, LED253.A, LED261.A, LED269.A, LED277.A, LED285.A, LED293.A, LED301.A, LED309.A, U2.19
unnamed: LED4.A, LED12.A, LED20.A, LED28.A, LED36.A, LED44.A, LED52.A, LED60.A, LED68.A, LED76.A, LED84.A, LED92.A, LED100.A, LED108.A, LED116.A, LED124.A, LED132.A, LED140.A, LED148.A, LED156.A, LED164.A, LED172.A, LED180.A, LED188.A, LED196.A, LED204.A, LED212.A, LED220.A, LED228.A, LED236.A, LED244.A, LED252.A, LED260.A, LED268.A, LED276.A, LED284.A, LED292.A, LED300.A, LED308.A, U2.20
unnamed: LED3.A, LED11.A, LED19.A, LED27.A, LED35.A, LED43.A, LED51.A, LED59.A, LED67.A, LED75.A, LED83.A, LED91.A, LED99.A, LED107.A, LED115.A, LED123.A, LED131.A, LED139.A, LED147.A, LED155.A, LED163.A, LED171.A, LED179.A, LED187.A, LED195.A, LED203.A, LED211.A, LED219.A, LED227.A, LED235.A, LED243.A, LED251.A, LED259.A, LED267.A, LED275.A, LED283.A, LED291.A, LED299.A, LED307.A, U2.21
unnamed: LED2.A, LED10.A, LED18.A, LED26.A, LED34.A, LED42.A, LED50.A, LED58.A, LED66.A, LED74.A, LED82.A, LED90.A, LED98.A, LED106.A, LED114.A, LED122.A, LED130.A, LED138.A, LED146.A, LED154.A, LED162.A, LED170.A, LED178.A, LED186.A, LED194.A, LED202.A, LED210.A, LED218.A, LED226.A, LED234.A, LED242.A, LED250.A, LED258.A, LED266.A, LED274.A, LED282.A, LED290.A, LED298.A, LED306.A, U2.22
unnamed: LED1.A, LED9.A, LED17.A, LED25.A, LED33.A, LED41.A, LED49.A, LED57.A, LED65.A, LED73.A, LED81.A, LED89.A, LED97.A, LED105.A, LED113.A, LED121.A, LED129.A, LED137.A, LED145.A, LED153.A, LED161.A, LED169.A, LED177.A, LED185.A, LED193.A, LED201.A, LED209.A, LED217.A, LED225.A, LED233.A, LED241.A, LED249.A, LED257.A, LED265.A, LED273.A, LED281.A, LED289.A, LED297.A, LED305.A, U2.23
SCL: J4.2, U1.10, U2.10
SDA: J4.1, U1.9, U2.9
SW6: LED315.A, LED323.A, LED331.A, LED339.A, LED347.A, LED355.A, LED363.A, LED371.A, LED379.A, LED387.A, LED395.A, LED403.A, LED411.A, LED419.A, LED427.A, LED435.A, LED443.A, LED451.A, LED459.A, LED467.A, LED475.A, LED483.A, LED491.A, LED499.A, LED507.A, LED515.A, LED523.A, LED531.A, LED539.A, LED547.A, LED555.A, LED563.A, LED571.A, LED579.A, LED587.A, LED595.A, LED603.A, LED611.A, LED619.A, U1.21
SW7: LED314.A, LED322.A, LED330.A, LED338.A, LED346.A, LED354.A, LED362.A, LED370.A, LED378.A, LED386.A, LED394.A, LED402.A, LED410.A, LED418.A, LED426.A, LED434.A, LED442.A, LED450.A, LED458.A, LED466.A, LED474.A, LED482.A, LED490.A, LED498.A, LED506.A, LED514.A, LED522.A, LED530.A, LED538.A, LED546.A, LED554.A, LED562.A, LED570.A, LED578.A, LED586.A, LED594.A, LED602.A, LED610.A, LED618.A, U1.22
SW8: LED313.A, LED321.A, LED329.A, LED337.A, LED345.A, LED353.A, LED361.A, LED369.A, LED377.A, LED385.A, LED393.A, LED401.A, LED409.A, LED417.A, LED425.A, LED433.A, LED441.A, LED449.A, LED457.A, LED465.A, LED473.A, LED481.A, LED489.A, LED497.A, LED505.A, LED513.A, LED521.A, LED529.A, LED537.A, LED545.A, LED553.A, LED561.A, LED569.A, LED577.A, LED585.A, LED593.A, LED601.A, LED609.A, LED617.A, U1.23
VCC: C1.1, C2.1, C3.1, C4.1, C5.1, C6.1, C7.1, C8.1, C9.1, C10.1, C11.1, C12.1, J4.4, U1.14, U1.15, U1.25, U2.14, U2.15, U2.25

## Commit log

2022-12-08 update, gerbers
2022-12-13 update led panel
2023-02-06 finished board

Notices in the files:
parts and their libraries:
SparkFun-Connectors: Licensing: Creative Commons ShareAlike 4.0 International - https://creativecommons.org/licenses/by-sa/4.0
COPYRIGHT: Copyright (C) 2023 Ultra Librarian. All rights reserved.
